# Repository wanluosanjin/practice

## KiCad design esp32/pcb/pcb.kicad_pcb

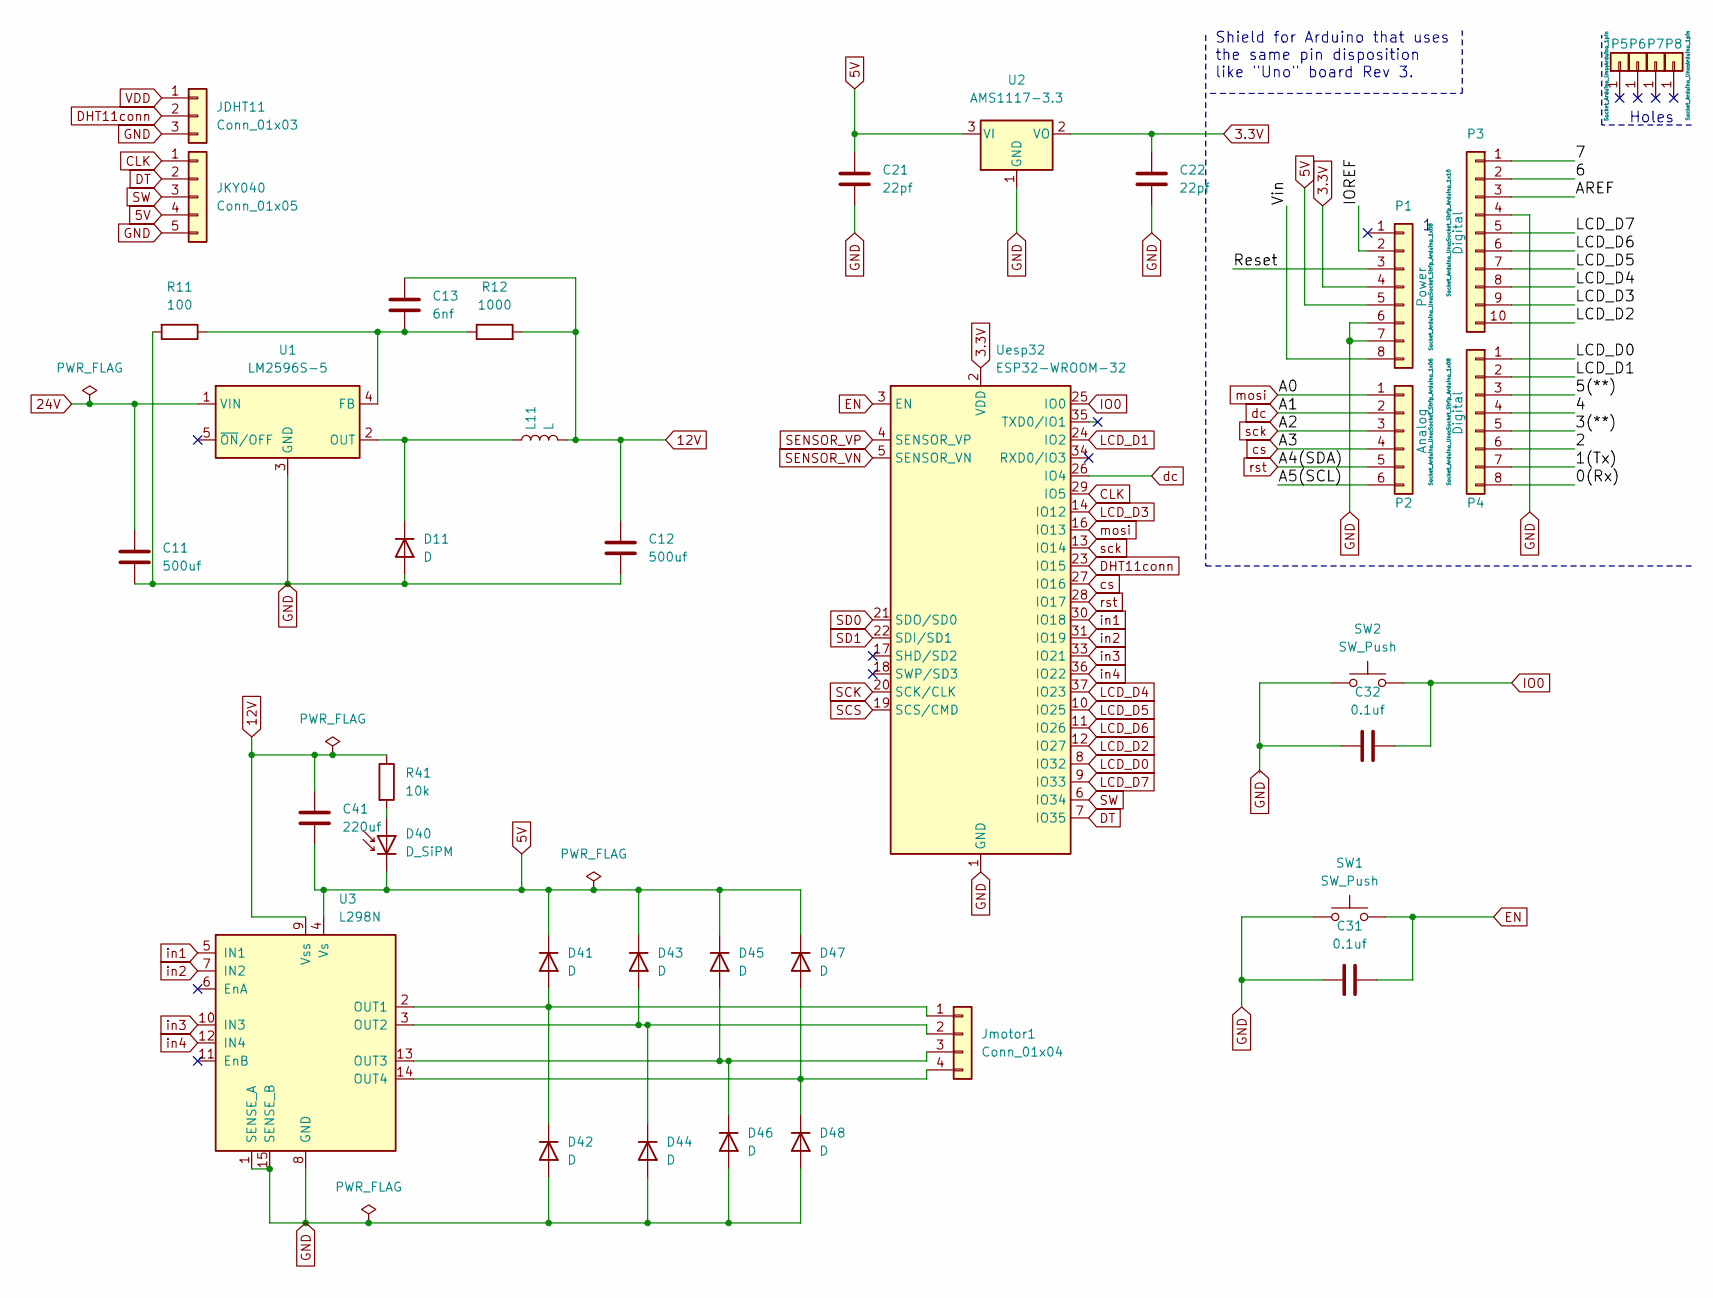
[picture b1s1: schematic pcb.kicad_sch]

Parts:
C11, C12: 500uf; C_Elec_5x5.8
C13: 6nf; C_1206_3216Metric_Pad1.33x1.80mm_HandSolder
C21, C22: 22pf; C_1206_3216Metric
C31, C32: 0.1uf; C_1206_3216Metric_Pad1.33x1.80mm_HandSolder
C41: 220uf; C_1206_3216Metric
D11, D41, D42, D43, D44, D45, D46, D47, D48: D; D_MELF
D40: D_SiPM; C_Radial_D5.0mm_H11.0mm_P2.00mm
JDHT11: Conn_01x03; JST_EH_S3B-EH_1x03_P2.50mm_Horizontal
JKY040: Conn_01x05; JST_EH_S5B-EH_1x05_P2.50mm_Horizontal
Jmotor1: Conn_01x04; JST_EH_S4B-EH_1x04_P2.50mm_Horizontal
L11: L; L_7.3x7.3_H4.5
P1: Power; Socket_Strip_Arduino_1x08
P2: Analog; Socket_Strip_Arduino_1x06
P3: Digital; Socket_Strip_Arduino_1x10
P4: Digital; Socket_Strip_Arduino_1x08
P5, P6, P7, P8: CONN_01X01; Arduino_1pin
R11: 100; R_0603_1608Metric
R12: 1000; R_0603_1608Metric
R41: 10k; R_0603_1608Metric
SW1, SW2: SW_Push; SW_SPST_B3S-1000
U1: LM2596S-5; TO-263-5_TabPin3
U2: AMS1117-3.3; SOT-223-3_TabPin2
U3: L298N; TO-220-15_P2.54x2.54mm_StaggerOdd_Lead4.58mm_Vertical
Uesp32: ESP32-WROOM-32

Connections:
3.3V: C22.1, P1.4, U2.2 (VO), Uesp32.2 (VDD)
5V: C21.1, C41.2, D40.1 (K), D41.1 (K), D43.1 (K), D45.1 (K), D47.1 (K), JKY040.4, P1.5, U2.3 (VI), U3.4 (Vs)
12V: C12.1, C13.1, C41.1, L11.2, R12.2, R41.1, U3.9 (Vss)
24V: C11.1, U1.1 (VIN)
/0(Rx): P4.8
/1(Tx): P4.7
/2: P4.6
/3(**): P4.5
/4: P4.4
/5(**): P4.3
/6(**): P4.2
/7: P4.1
/8: P3.10
/9(**): P3.9
/10(**/SS): P3.8
/11(**/MOSI): P3.7
/12(MISO): P3.6
/13(SCK): P3.5
/AREF: P3.3
/IOREF: P1.2
/Reset: P1.3
/Vin: P1.8
CLK: JKY040.1, Uesp32.29 (IO5)
DHT11conn: JDHT11.2, Uesp32.23 (IO15)
DT: JKY040.2, Uesp32.7 (IO35)
EN: C31.1, SW1.2, Uesp32.3 (EN)
GND: C11.2, C12.2, C21.2, C22.2, C31.2, C32.2, D11.2 (A), D42.2 (A), D44.2 (A), D46.2 (A), D48.2 (A), JDHT11.3, JKY040.5, P1.6, P1.7, P3.4, R11.2, SW1.1, SW2.1, U1.3 (GND), U2.1 (GND), U3.1 (SENSE_A), U3.8 (GND), U3.15 (SENSE_B), Uesp32.1 (GND), Uesp32.15 (GND), Uesp32.38 (GND), Uesp32.39 (GND)
IO0: C32.1, SW2.2, Uesp32.25 (IO0)
LCD_D0: Uesp32.8 (IO32)
LCD_D1: Uesp32.24 (IO2)
LCD_D2: Uesp32.12 (IO27)
LCD_D3: Uesp32.14 (IO12)
LCD_D4: Uesp32.37 (IO23)
LCD_D5: Uesp32.10 (IO25)
LCD_D6: Uesp32.11 (IO26)
LCD_D7: Uesp32.9 (IO33)
unnamed: C13.2, R11.1, R12.1, U1.4 (FB)
unnamed: D11.1 (K), L11.1, U1.2 (OUT)
unnamed: D40.2 (A), R41.2
unnamed: D41.2 (A), D42.1 (K), Jmotor1.1, U3.2 (OUT1)
unnamed: D43.2 (A), D44.1 (K), Jmotor1.2, U3.3 (OUT2)
unnamed: D45.2 (A), D46.1 (K), Jmotor1.3, U3.13 (OUT3)
unnamed: D47.2 (A), D48.1 (K), Jmotor1.4, U3.14 (OUT4)
SCK: Uesp32.20 (SCK/CLK)
SCS: Uesp32.19 (SCS/CMD)
SD0: Uesp32.21 (SDO/SD0)
SD1: Uesp32.22 (SDI/SD1)
SENSOR_VN: Uesp32.5 (SENSOR_VN)
SENSOR_VP: Uesp32.4 (SENSOR_VP)
SW: JKY040.3, Uesp32.6 (IO34)
VDD: JDHT11.1
cs: P2.4, Uesp32.27 (IO16)
dc: P2.2, Uesp32.26 (IO4)
in1: U3.5 (IN1), Uesp32.30 (IO18)
in2: U3.7 (IN2), Uesp32.31 (IO19)
in3: U3.10 (IN3), Uesp32.33 (IO21)
in4: U3.12 (IN4), Uesp32.36 (IO22)
mosi: P2.1, Uesp32.16 (IO13)
sck: P2.3, Uesp32.13 (IO14)

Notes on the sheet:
Holes
Shield for Arduino that uses the same pin disposition like "Uno" board Rev 3.

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
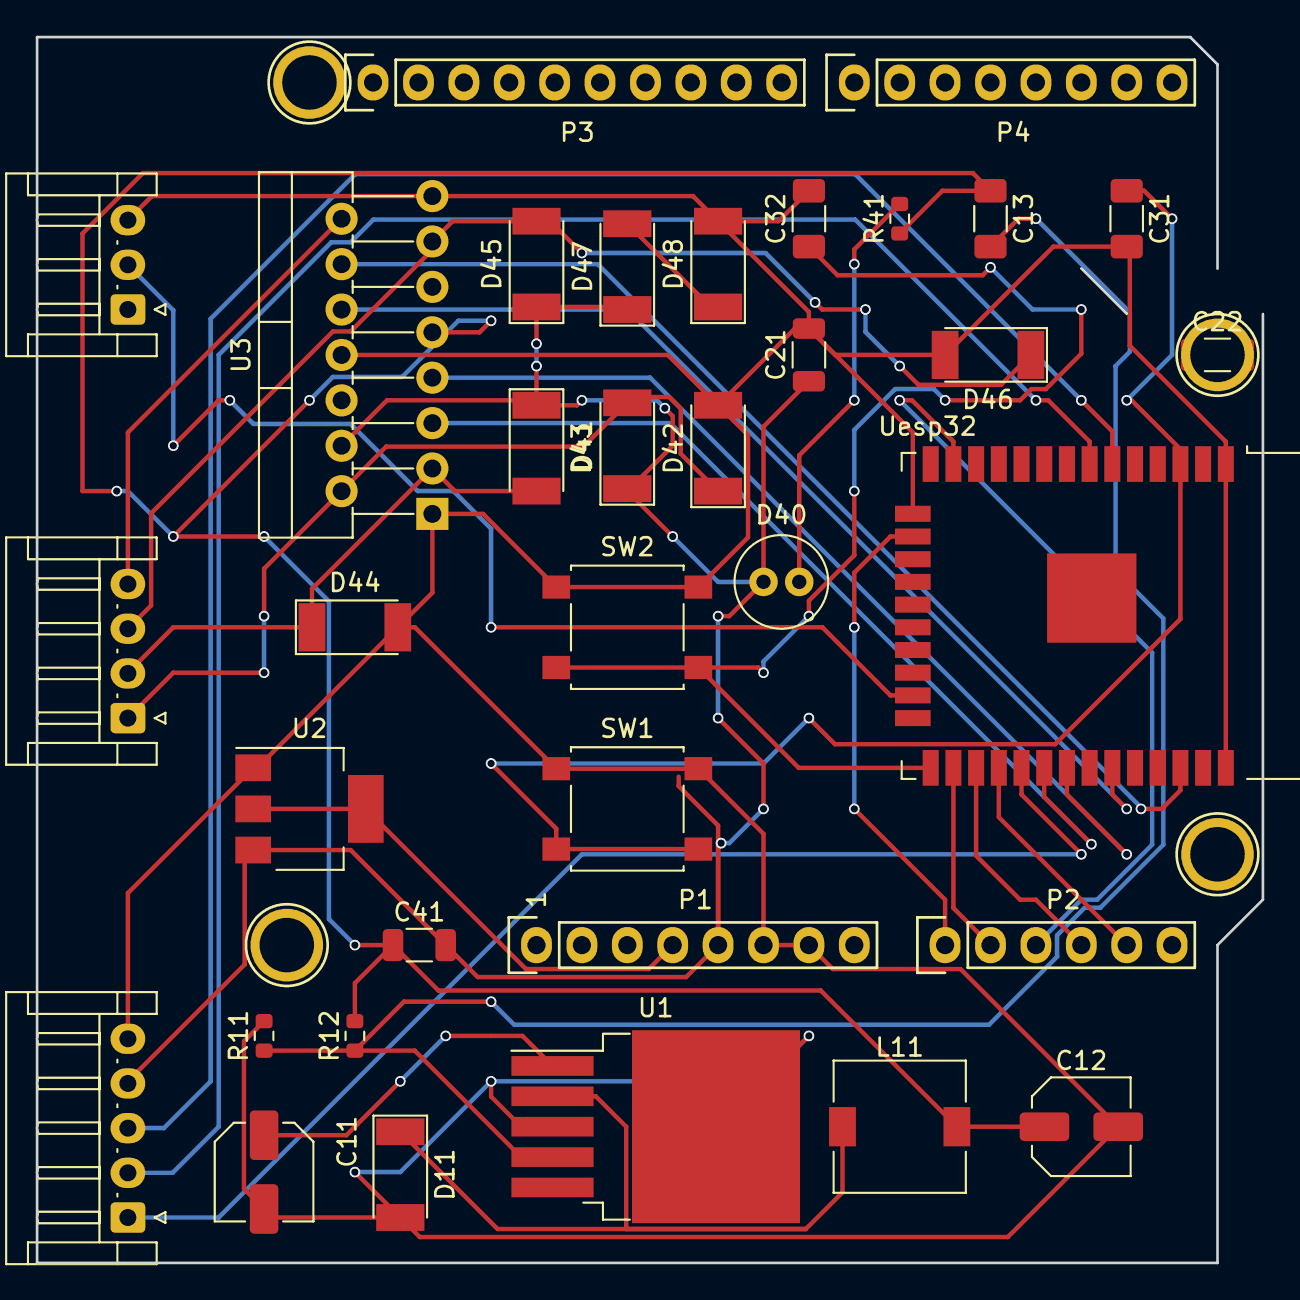
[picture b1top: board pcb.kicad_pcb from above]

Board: 2 copper layers, 68.6 x 68.6 mm, 39 parts (0 on the bottom side), 28 nets.

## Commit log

2022-03-13 deleted: cJSON.c deleted: cJSON.h deleted: cJSON_Utils.c deleted: cJSON_Utils.h deleted: fs modified: makefile modified: myhead.h modified: myshell.sh
2022-03-13 new file: .emacs
2022-03-13 deleted: lib/cJSON.c
2022-03-13 del .emacs.d
2022-08-14 renamed: game/a2.cpp -> aaa/a2.cpp new file: aaa/aaa.cpp renamed: void.cpp -> aaa/json.cpp renamed: reader.cpp -> "aaa/json\345\256\236\351\252\214.cpp" renamed: game/ls.strace -> aaa/ls.strace
2023-11-29 js add
2023-11-30 new : vs
2023-12-07 Create c-cpp.yml
    defaut make
2024-04-18 del class
2026-06-27 Update Emacs configuration with new keybindings and themes
